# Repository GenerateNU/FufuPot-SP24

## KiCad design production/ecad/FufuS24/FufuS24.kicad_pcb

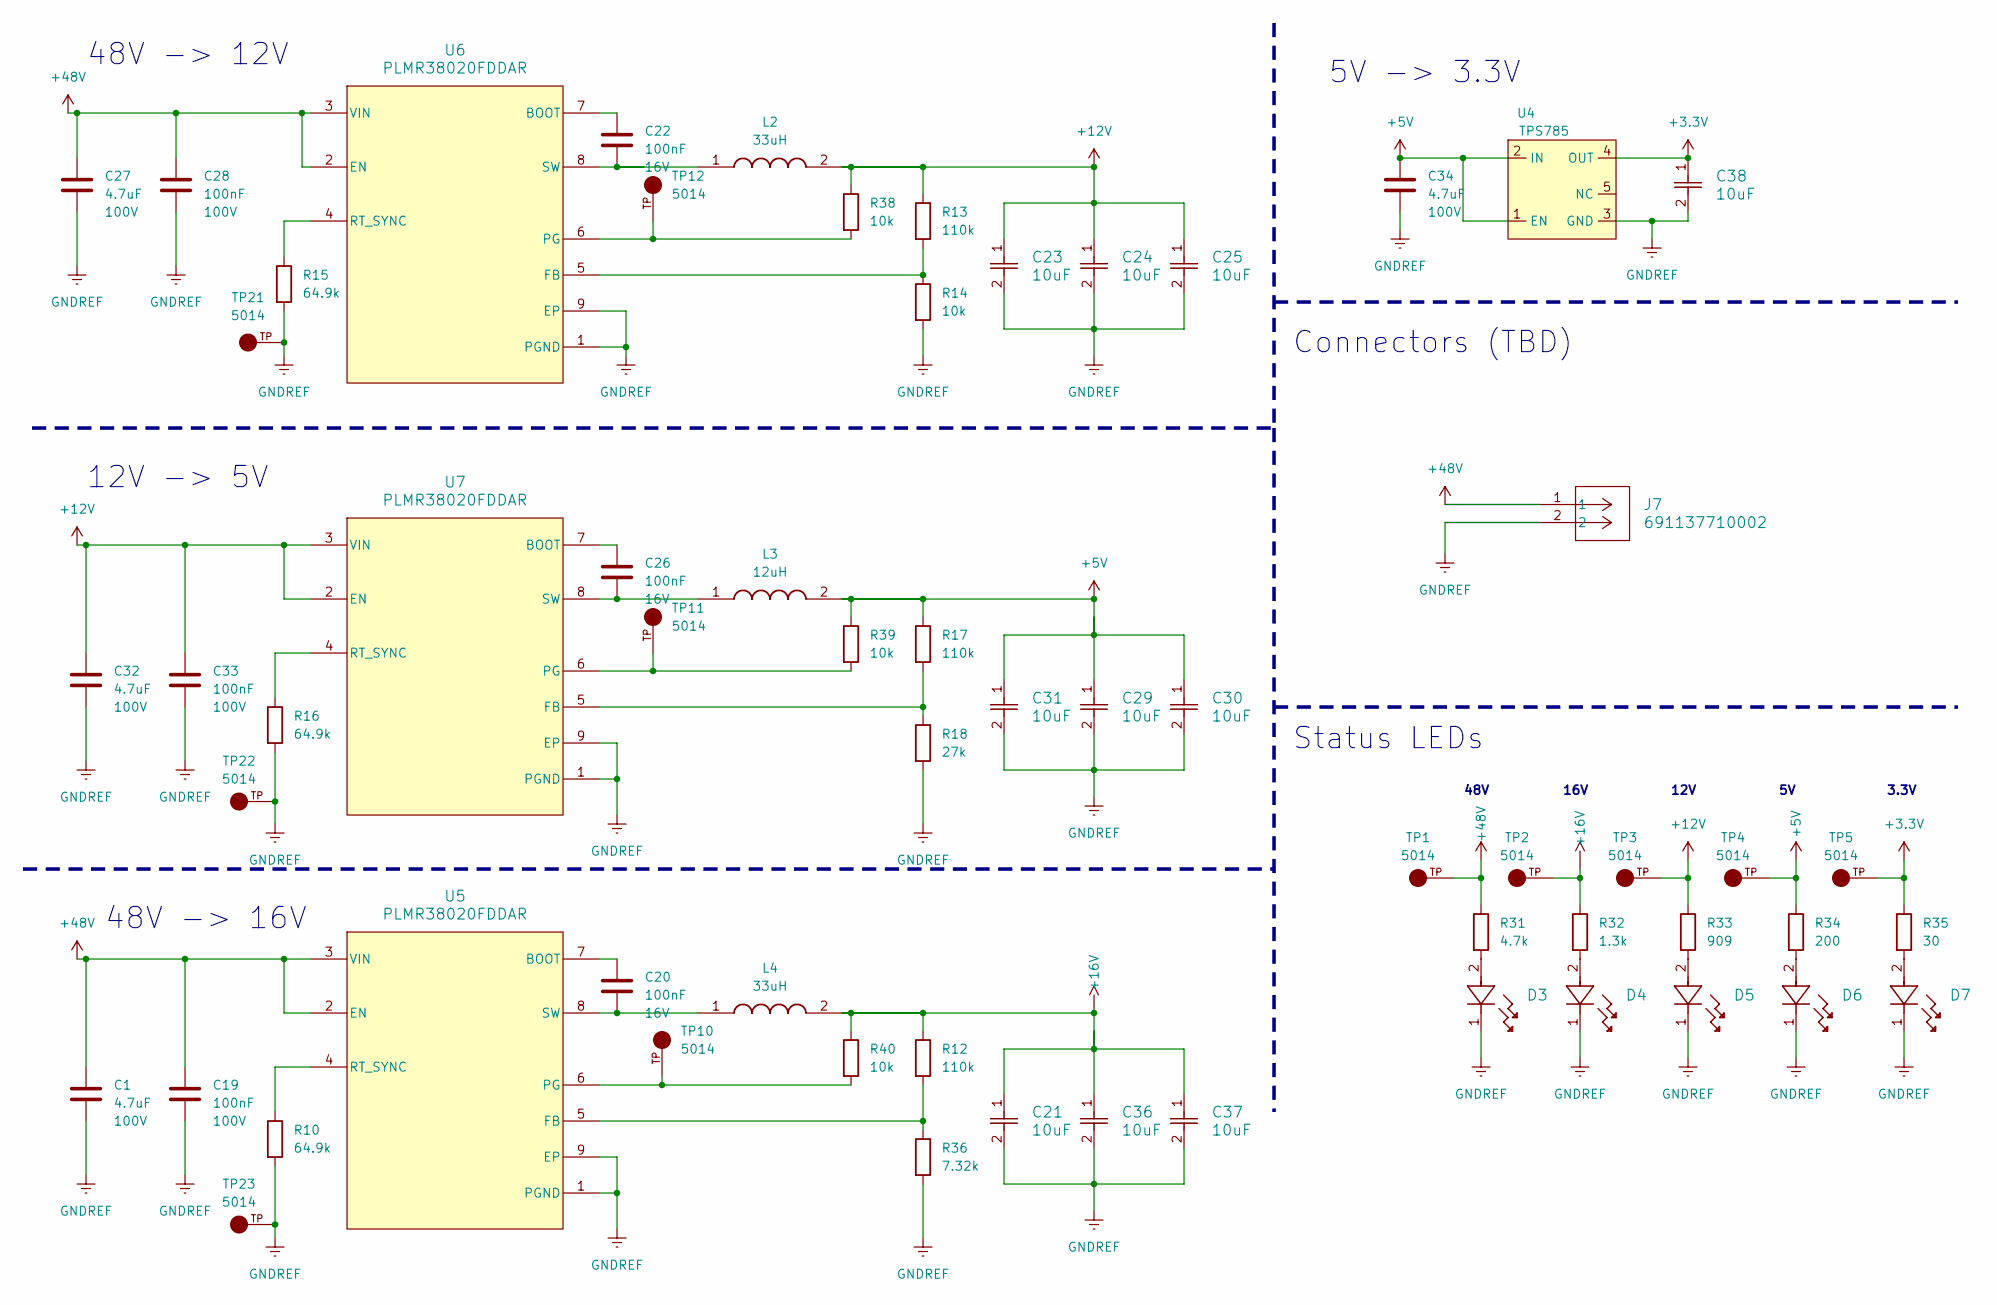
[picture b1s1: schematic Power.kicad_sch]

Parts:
C1, C27, C32, C34: 4.7uF; C_1210_3225Metric; Voltage 100V; MPN KAM32LR72A475KU
C19, C28, C33: 100nF; CAPC2012X94N; Voltage 100V; MPN CL21B104KCFNNNE
C20, C22, C26: 100nF; CAPC2012X94N; Voltage 16V; MPN CL21B104KCFNNNE
C21, C23, C24, C25, C29, C30, C31, C36, C37, C38: 10uF; CAPC2012X94N
D3, D4, D5, D6, D7: 150080GS75000; LED_GS75000_WRE
J7: 691137710002; CONN2_710002_WRE
L2, L4: 33uH; INDPM120120X800N; Manufacturer_Part_Number CDRH127/LDNP-330MC; Mouser Part Number 851-CDRH127LDNP330MC
L3: 12uH; INDPM120120X800N; Manufacturer_Part_Number CDRH127/LDNP-120MC; Mouser Part Number 851-CDRH127LDNP120MC
R10, R15, R16: 64.9k; RESC2012X60N
R12, R13, R17: 110k; RESC2012X60N
R14, R38, R39, R40: 10k; RESC2012X60N
R18: 27k; RESC2012X60N
R31: 4.7k; RESC2012X60N
R32: 1.3k; RESC2012X60N
R33: 909; RESC2012X60N
R34: 200; RESC2012X60N
R35: 30; RESC2012X60N
R36: 7.32k; RESC2012X60N
TP1, TP2, TP3, TP4, TP5, TP10, TP11, TP12, TP21, TP22, TP23: 5014; TP_5014; PARTREV F
U4: TPS785; DPAK114P990X239-6N
U5, U6, U7: PLMR38020FDDAR; DDA0008E-IPC_A

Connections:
+12V: C23.1, C24.1, C25.1, C32.1, C33.1, L2.2, R13.1, R33.1, R38.1, TP3.TP, U7.2 (EN), U7.3 (VIN); also elsewhere on the board
+16V: C21.1, C36.1, C37.1, L4.2, R12.1, R32.1, R40.1, TP2.TP; also elsewhere on the board
+48V: C1.1, C19.1, C27.1, C28.1, J7.1, R31.1, TP1.TP, U5.2 (EN), U5.3 (VIN), U6.2 (EN), U6.3 (VIN); also elsewhere on the board
unnamed: D3.2, R31.2
unnamed: D4.2, R32.2
unnamed: D5.2, R33.2
unnamed: D6.2, R34.2
unnamed: D7.2, R35.2
unnamed: C20.1, U5.7 (BOOT)
unnamed: R12.2, R36.1, U5.5 (FB)
unnamed: R40.2, TP10.TP, U5.6 (PG)
unnamed: R10.1, U5.4 (RT_SYNC)
unnamed: C20.2, L4.1, U5.8 (SW)
unnamed: C22.1, U6.7 (BOOT)
unnamed: R13.2, R14.1, U6.5 (FB)
unnamed: R38.2, TP12.TP, U6.6 (PG)
unnamed: R15.1, U6.4 (RT_SYNC)
unnamed: C22.2, L2.1, U6.8 (SW)
unnamed: C26.1, U7.7 (BOOT)
unnamed: R17.2, R18.1, U7.5 (FB)
unnamed: R39.2, TP11.TP, U7.6 (PG)
unnamed: R16.1, U7.4 (RT_SYNC)
unnamed: C26.2, L3.1, U7.8 (SW)

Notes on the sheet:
16V
48V -> 12V
12V -> 5V
5V -> 3.3V
Status LEDs
48V -> 16V
48V
3.3V
Connectors (TBD)
12V

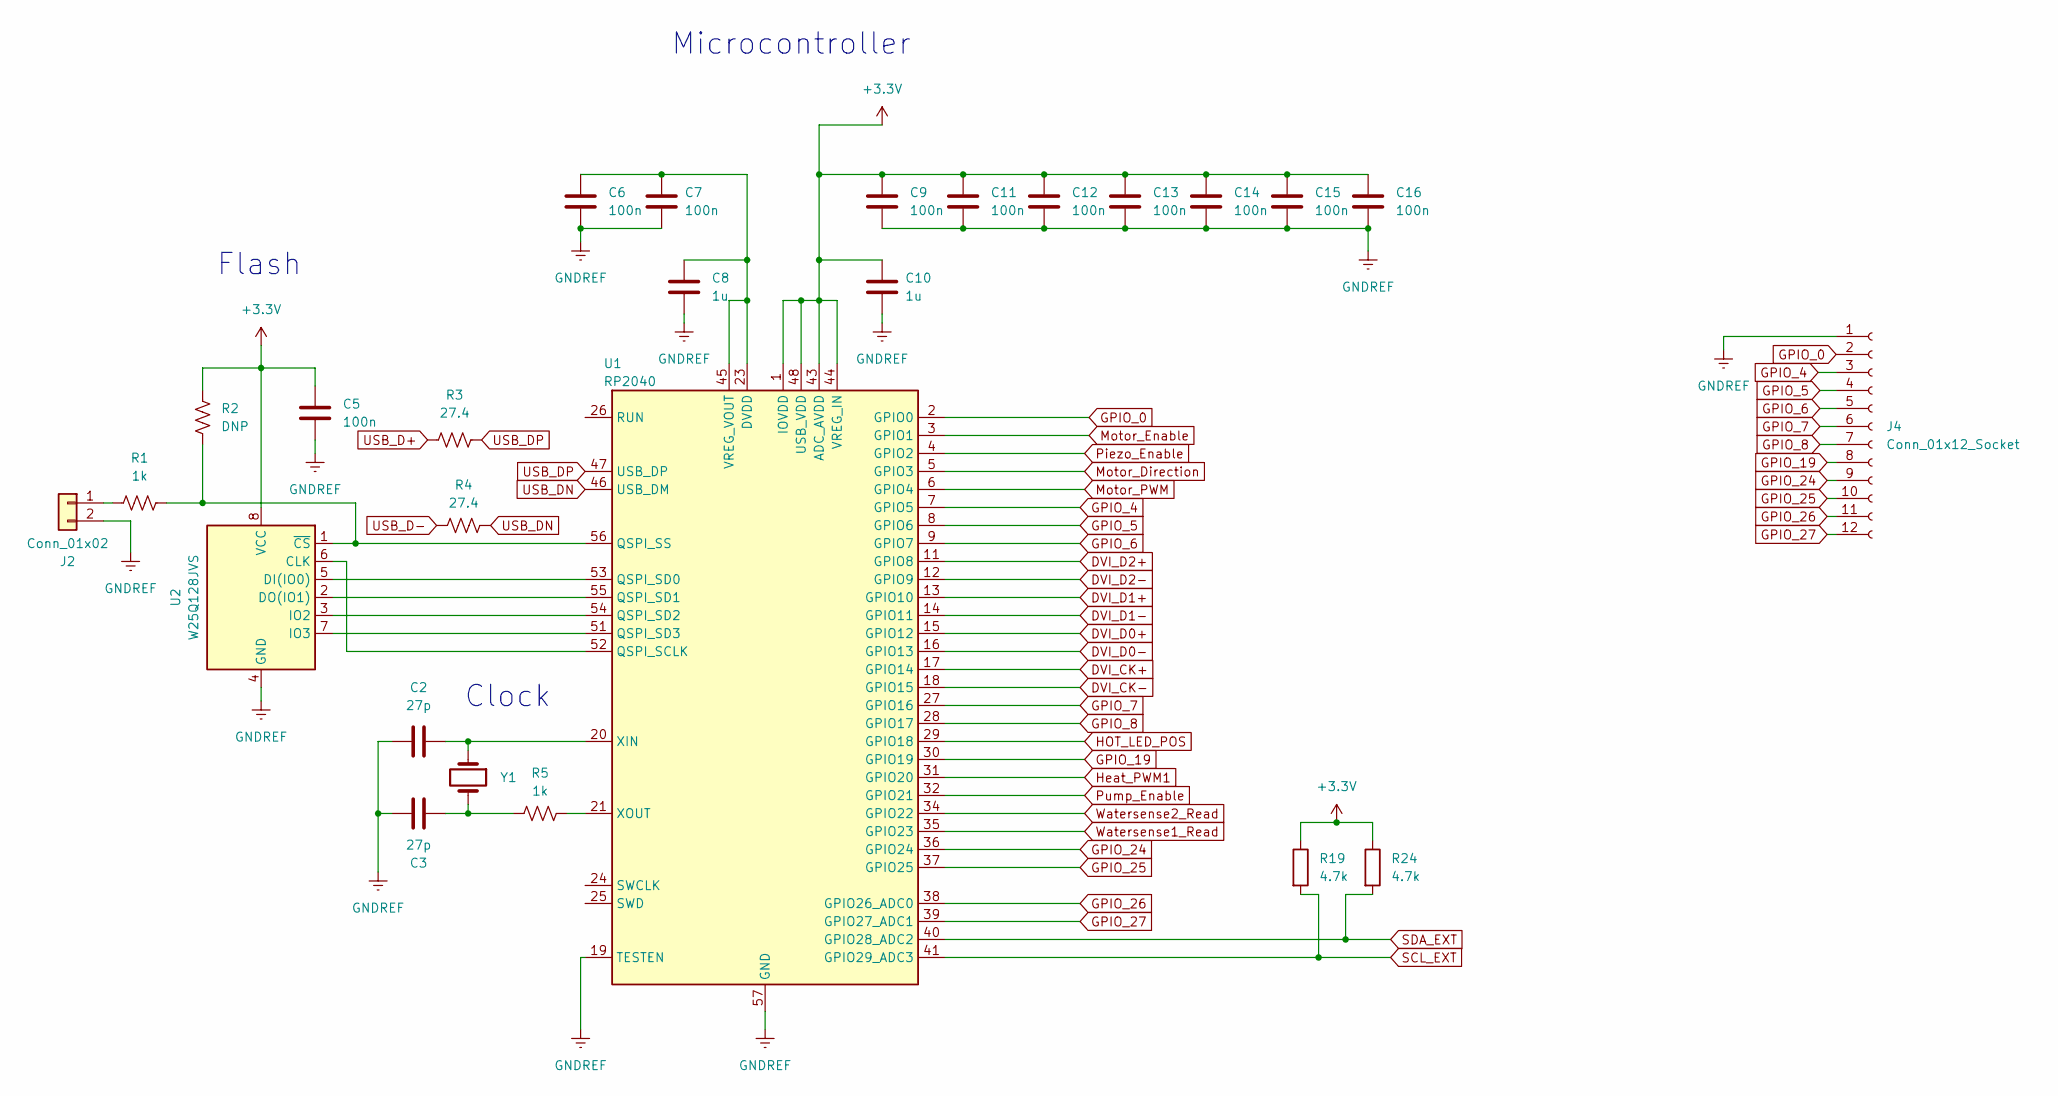
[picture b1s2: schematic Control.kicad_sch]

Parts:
C2, C3: 27p; CAPC2012X94N
C5, C6, C7, C9, C11, C12, C13, C14, C15, C16: 100n; CAPC2012X94N
C8, C10: 1u; CAPC2012X94N
J2: Conn_01x02; CON_5025840270_MOL
J4: Conn_01x12_Socket; PinSocket_1x12_P2.54mm_Vertical
R1, R5: 1k; RESC2012X60N
R2: DNP; RESC2012X60N
R3, R4: 27.4; RESC2012X60N
R19, R24: 4.7k; RESC2012X60N
U1: RP2040; RP2040_Footprint
U2: W25Q128JVS; W25Q128JVSIM_footprint
Y1: XTAL_ABLS-12.000MHZ-B4-T

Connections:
DVI_CK+: U1.17 (GPIO14); also elsewhere on the board
DVI_CK-: U1.18 (GPIO15); also elsewhere on the board
DVI_D0+: U1.15 (GPIO12); also elsewhere on the board
DVI_D0-: U1.16 (GPIO13); also elsewhere on the board
DVI_D1+: U1.13 (GPIO10); also elsewhere on the board
DVI_D1-: U1.14 (GPIO11); also elsewhere on the board
DVI_D2+: U1.11 (GPIO8); also elsewhere on the board
DVI_D2-: U1.12 (GPIO9); also elsewhere on the board
GPIO_0: J4.2, U1.2 (GPIO0)
GPIO_4: J4.3, U1.7 (GPIO5)
GPIO_5: J4.4, U1.8 (GPIO6)
GPIO_6: J4.5, U1.9 (GPIO7)
GPIO_7: J4.6, U1.27 (GPIO16)
GPIO_8: J4.7, U1.28 (GPIO17)
GPIO_19: J4.8, U1.30 (GPIO19)
GPIO_24: J4.9, U1.36 (GPIO24)
GPIO_25: J4.10, U1.37 (GPIO25)
GPIO_26: J4.11, U1.38 (GPIO26_ADC0)
GPIO_27: J4.12, U1.39 (GPIO27_ADC1)
HOT_LED_POS: U1.29 (GPIO18); also elsewhere on the board
Heat_PWM1: U1.31 (GPIO20); also elsewhere on the board
Motor_Direction: U1.5 (GPIO3); also elsewhere on the board
Motor_Enable: U1.3 (GPIO1); also elsewhere on the board
Motor_PWM: U1.6 (GPIO4); also elsewhere on the board
unnamed: C3.2, R5.1, Y1.2
unnamed: J2.1, R1.1
unnamed: U1.52 (QSPI_SCLK), U2.6 (CLK)
unnamed: U1.53 (QSPI_SD0), U2.5 (DI(IO0))
unnamed: U1.55 (QSPI_SD1), U2.2 (DO(IO1))
unnamed: U1.54 (QSPI_SD2), U2.3 (IO2)
unnamed: U1.51 (QSPI_SD3), U2.7 (IO3)
unnamed: R1.2, R2.1, U1.56 (QSPI_SS), U2.1 (~CS)
unnamed: C6.1, C7.1, C8.1, U1.23 (DVDD), U1.45 (VREG_VOUT), U1.50 (DVDD)
unnamed: C2.2, U1.20 (XIN), Y1.1
unnamed: R5.2, U1.21 (XOUT)
Piezo_Enable: U1.4 (GPIO2); also elsewhere on the board
Pump_Enable: U1.32 (GPIO21); also elsewhere on the board
SCL_EXT: R19.2, U1.41 (GPIO29_ADC3); also elsewhere on the board
SDA_EXT: R24.2, U1.40 (GPIO28_ADC2); also elsewhere on the board
USB_D+: R3.1; also elsewhere on the board
USB_D-: R4.1; also elsewhere on the board
USB_DN: R4.2, U1.46 (USB_DM)
USB_DP: R3.2, U1.47 (USB_DP)
Watersense1_Read: U1.35 (GPIO23); also elsewhere on the board
Watersense2_Read: U1.34 (GPIO22); also elsewhere on the board

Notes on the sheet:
Microcontroller
Flash
Clock

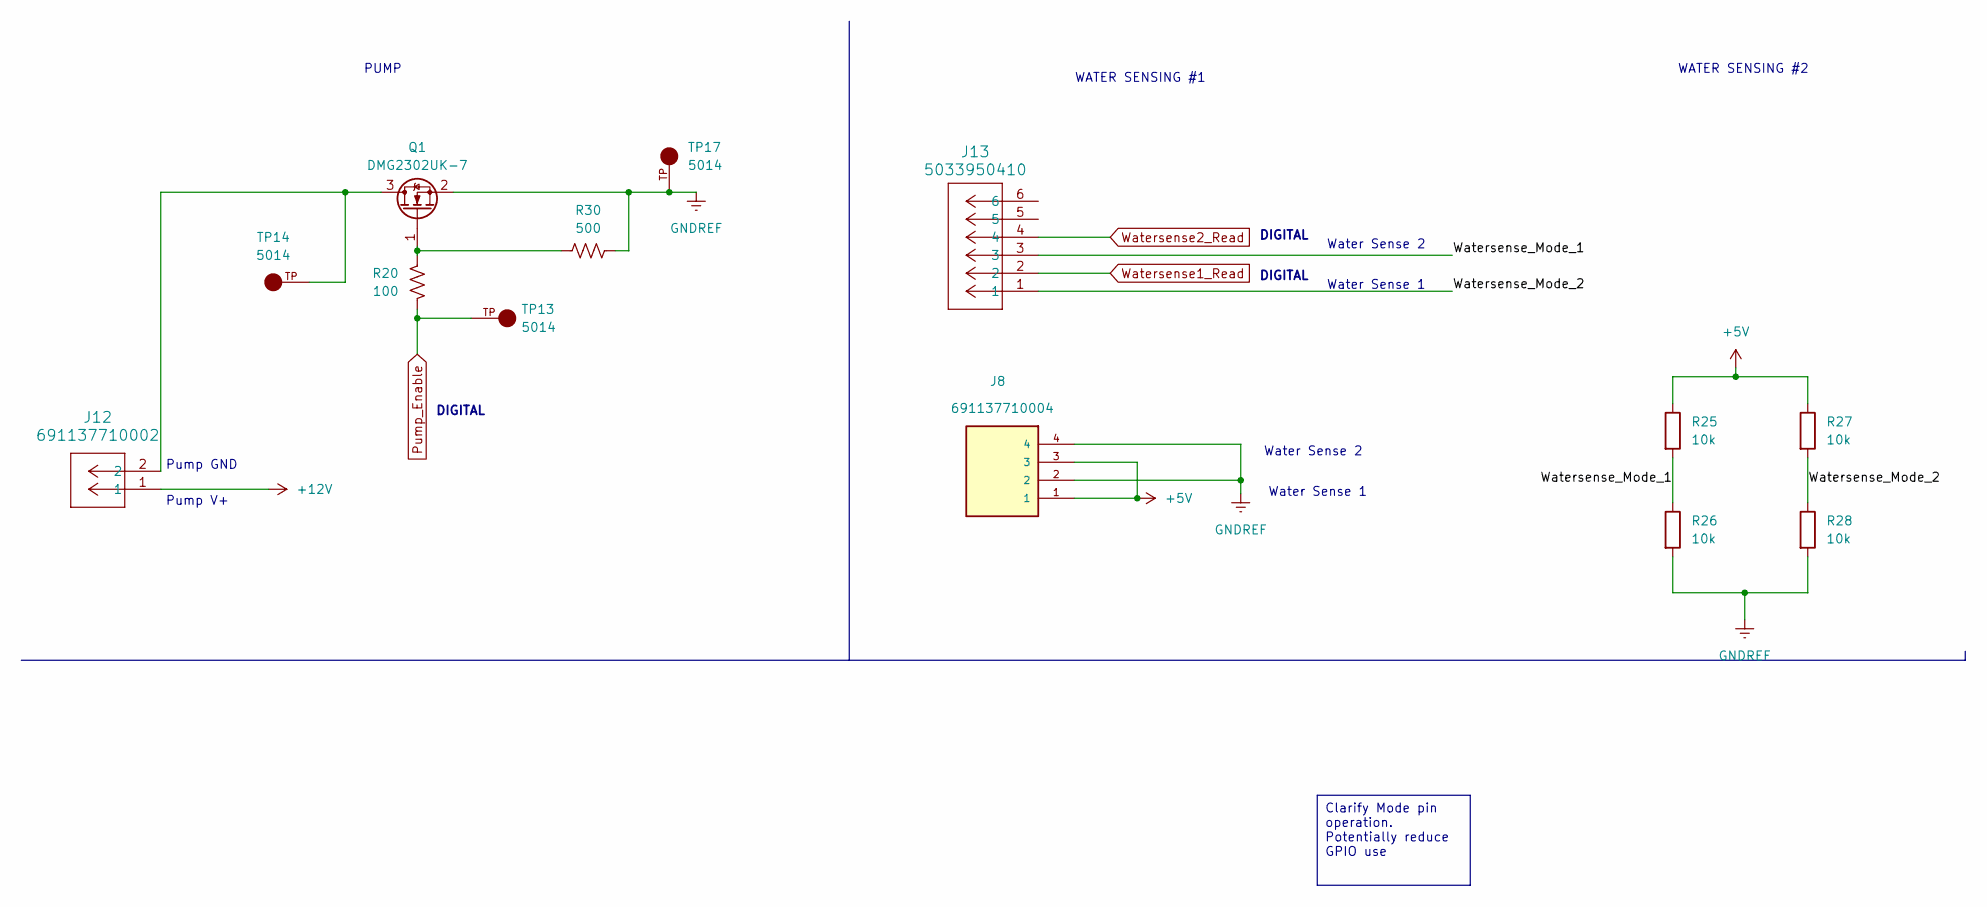
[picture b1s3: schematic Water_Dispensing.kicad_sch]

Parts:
J8: 691137710004; PWR_4POS; PARTREV 001
J12: 691137710002; CONN2_710002_WRE
J13: 5033950410; MOLEX4_CON_5033950410
Q1: DMG2302UK-7; DMG2302UK-7_Footprint
R20: 100; RESC2012X60N
R25, R26, R27, R28: 10k; RESC2012X60N
R30: 500; RESC2012X60N
TP13, TP14, TP17: 5014; TP_5014; PARTREV F

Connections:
+12V: J12.1; also elsewhere on the board
unnamed: J12.2, Q1.3 (D), TP14.TP
unnamed: Q1.1 (G), R20.1, R30.1
Pump_Enable: R20.2, TP13.TP; also elsewhere on the board
Watersense1_Read: J13.2; also elsewhere on the board
Watersense2_Read: J13.4; also elsewhere on the board

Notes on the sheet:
Clarify Mode pin operation. Potentially reduce GPIO use
Water Sense 1
Pump V+
PUMP
Water Sense 2
WATER SENSING #1
DIGITAL
Pump GND
WATER SENSING #2

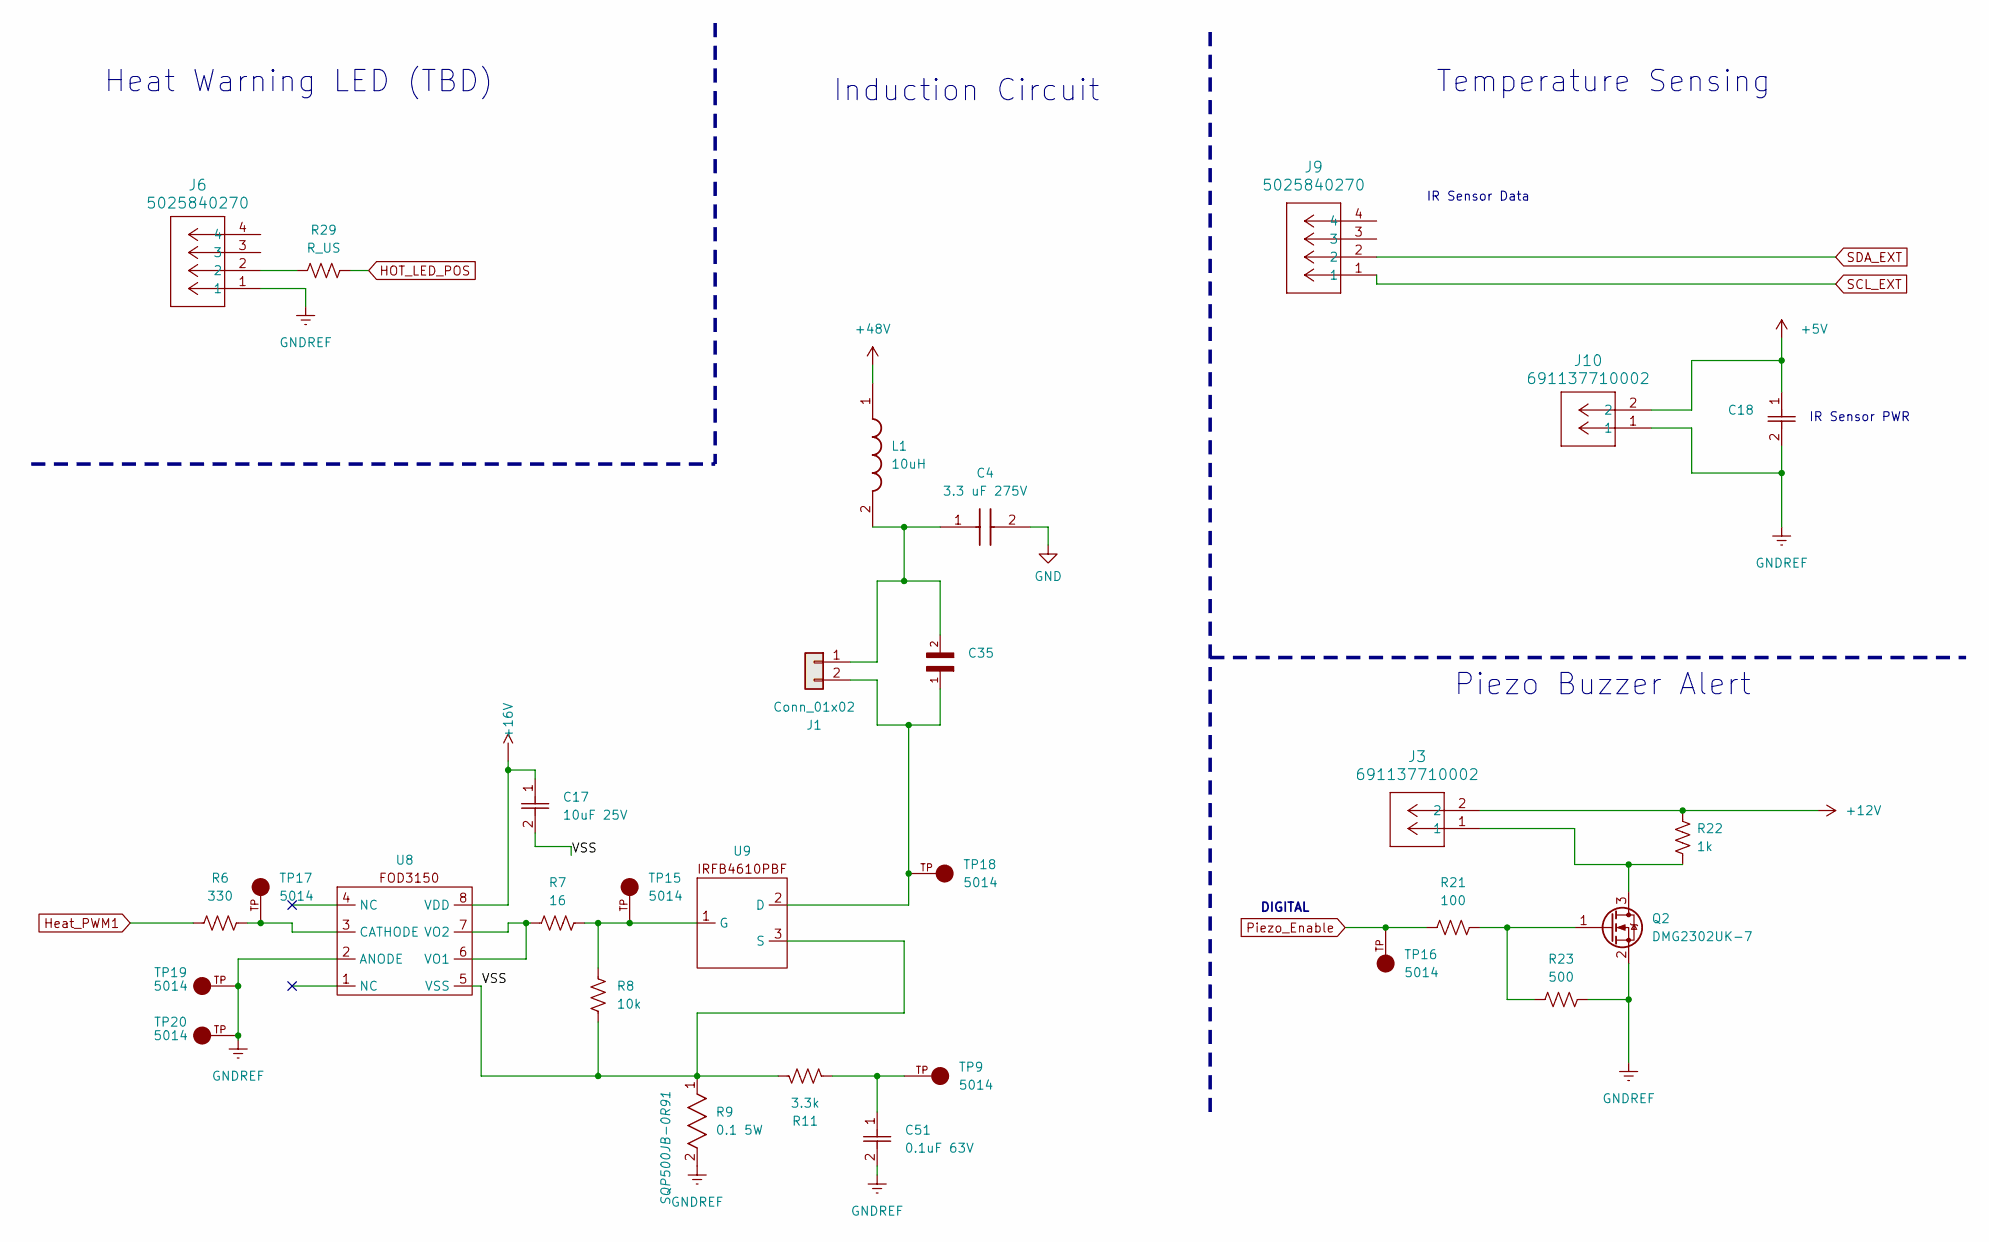
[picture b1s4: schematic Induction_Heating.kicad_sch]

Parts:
C4: 3.3 uF 275V; CAP_ECQUA_41.0LX15.0TX30.0H_PAN; Manufacturer_Part_Number ECQUAAF335LD
C17: 10uF 25V; CAPC2012X94N
C18, C51: 0.1uF 63V; CAPC2012X94N
C35: ECWF6754HL; CAPRR2500W80L2800T1330H1990; PARTREV 11-Oct-17
J1: Conn_01x02; CONN2_710002_WRE
J3, J10: 691137710002; CONN2_710002_WRE
J6, J9: 5025840270; CON_5025840270_MOL
L1: 10uH; INDPM120120X800N; Manufacturer_Part_Number SRP1770CC-100M
Q2: DMG2302UK-7; DMG2302UK-7_Footprint
R6: 330; RESC2012X60N
R7: 16; RESC2012X60N
R8: 10k; RESC2012X60N
R9: 0.1 5W; RES_SQP500_22X9P5_YAG
R11: 3.3k; RESC2012X60N
R21: 100; RESC2012X60N
R22: 1k; RESC2012X60N
R23: 500; RESC2012X60N
R29: R_US; RESC2012X60N
TP9, TP15, TP16, TP17, TP18, TP19, TP20: 5014; TP_5014; PARTREV F
U8: FOD3150_footprint
U9: IRFB4610PBF

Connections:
+12V: J3.2, R22.1; also elsewhere on the board
+16V: C17.1, U8.8 (VDD); also elsewhere on the board
+48V: L1.1; also elsewhere on the board
/Induction Heating/VSS: C17.2, R8.1, R9.1, R11.1, U8.5 (VSS), U9.3 (S)
GND: C4.2
HOT_LED_POS: R29.2; also elsewhere on the board
Heat_PWM1: R6.1; also elsewhere on the board
unnamed: C51.1, R11.2, TP9.TP
unnamed: C4.1, C35.2, J1.1, L1.2
unnamed: C35.1, J1.2, TP18.TP, U9.2 (D)
unnamed: J6.2, R29.1
unnamed: J3.1, Q2.3 (D), R22.2
unnamed: Q2.1 (G), R21.2, R23.1
unnamed: R7.1, U8.6 (VO1), U8.7 (VO2)
unnamed: R7.2, R8.2, TP15.TP, U9.1 (G)
Piezo_Enable: R21.1, TP16.TP; also elsewhere on the board
SCL_EXT: J9.1; also elsewhere on the board
SDA_EXT: J9.2; also elsewhere on the board

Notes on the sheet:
DIGITAL
Heat Warning LED (TBD)
IR Sensor Data
IR Sensor PWR
Induction Circuit
Temperature Sensing
Piezo Buzzer Alert

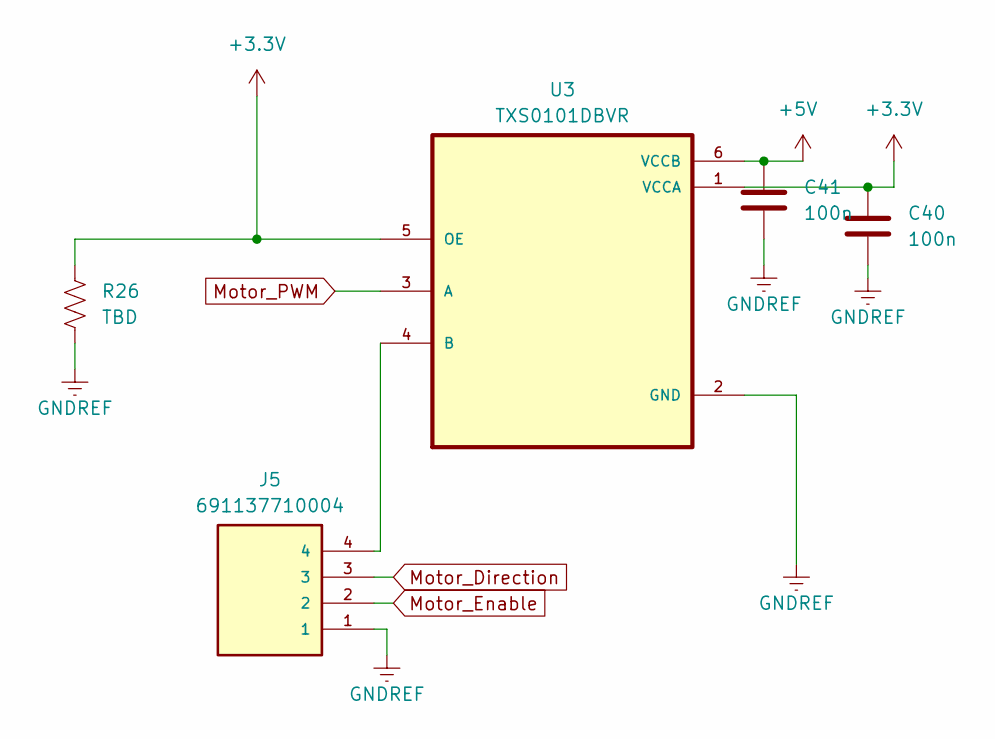
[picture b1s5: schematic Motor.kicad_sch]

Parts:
C40, C41: 100n; WCAP-CSGP_885012206026
J5: 691137710004; PWR_4POS; PARTREV 001
R26: TBD; RESC2012X60N
U3: TXS0101DBVR; LevelShifter_Motor

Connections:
Motor_Direction: J5.3; also elsewhere on the board
Motor_Enable: J5.2; also elsewhere on the board
Motor_PWM: U3.3 (A); also elsewhere on the board
unnamed: J5.4, U3.4 (B)

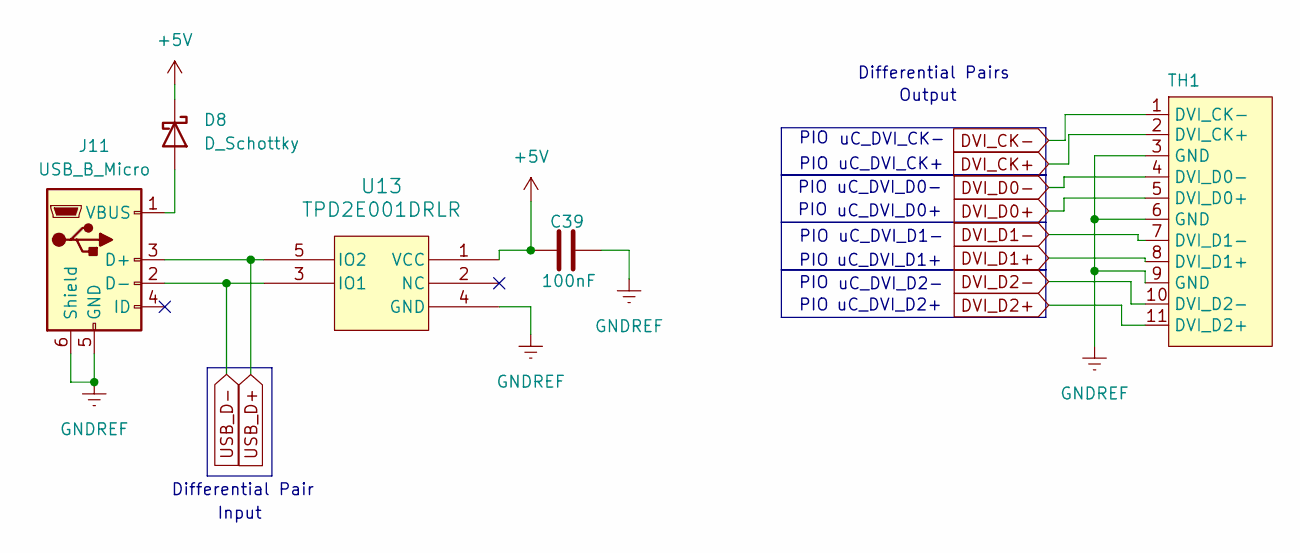
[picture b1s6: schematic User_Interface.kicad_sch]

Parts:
C39: 100nF; C_0805_2012Metric
D8: D_Schottky; D_SMA
J11: USB_B_Micro; USB_Micro-B_Molex-105017-0001
TH1: PinSocket_1x11_P2.54mm_Vertical
U13: TPD2E001DRLR; Texas_R-PDSO-N5_DRL-5

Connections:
DVI_CK+: TH1.2 (DVI_CK+); also elsewhere on the board
DVI_CK-: TH1.1 (DVI_CK-); also elsewhere on the board
DVI_D0+: TH1.5 (DVI_D0+); also elsewhere on the board
DVI_D0-: TH1.4 (DVI_D0-); also elsewhere on the board
DVI_D1+: TH1.8 (DVI_D1+); also elsewhere on the board
DVI_D1-: TH1.7 (DVI_D1-); also elsewhere on the board
DVI_D2+: TH1.11 (DVI_D2+); also elsewhere on the board
DVI_D2-: TH1.10 (DVI_D2-); also elsewhere on the board
USB_D+: J11.3 (D+), U13.5 (IO2); also elsewhere on the board
USB_D-: J11.2 (D-), U13.3 (IO1); also elsewhere on the board

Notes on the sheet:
Differential Pairs
PIO
uC_DVI_CK+
Input
uC_DVI_D0+
Output
uC_DVI_D1-
uC_DVI_D1+
uC_DVI_D0-
uC_DVI_D2-
uC_DVI_D2+
Differential Pair
uC_DVI_CK-

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
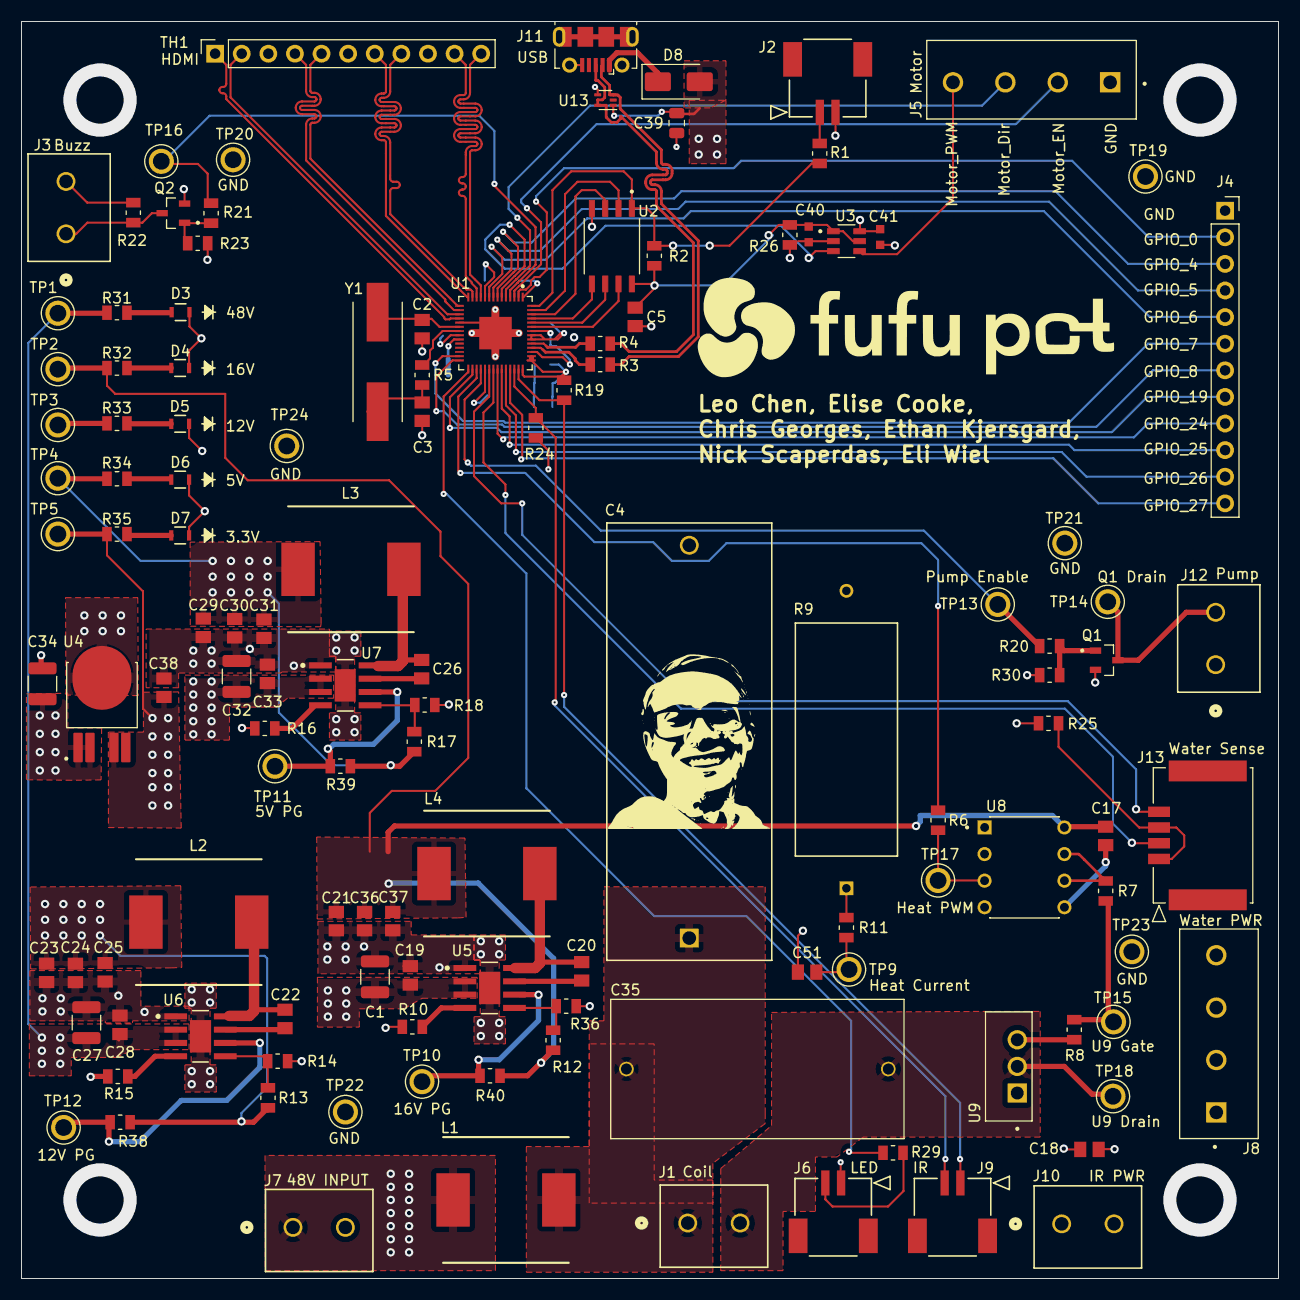
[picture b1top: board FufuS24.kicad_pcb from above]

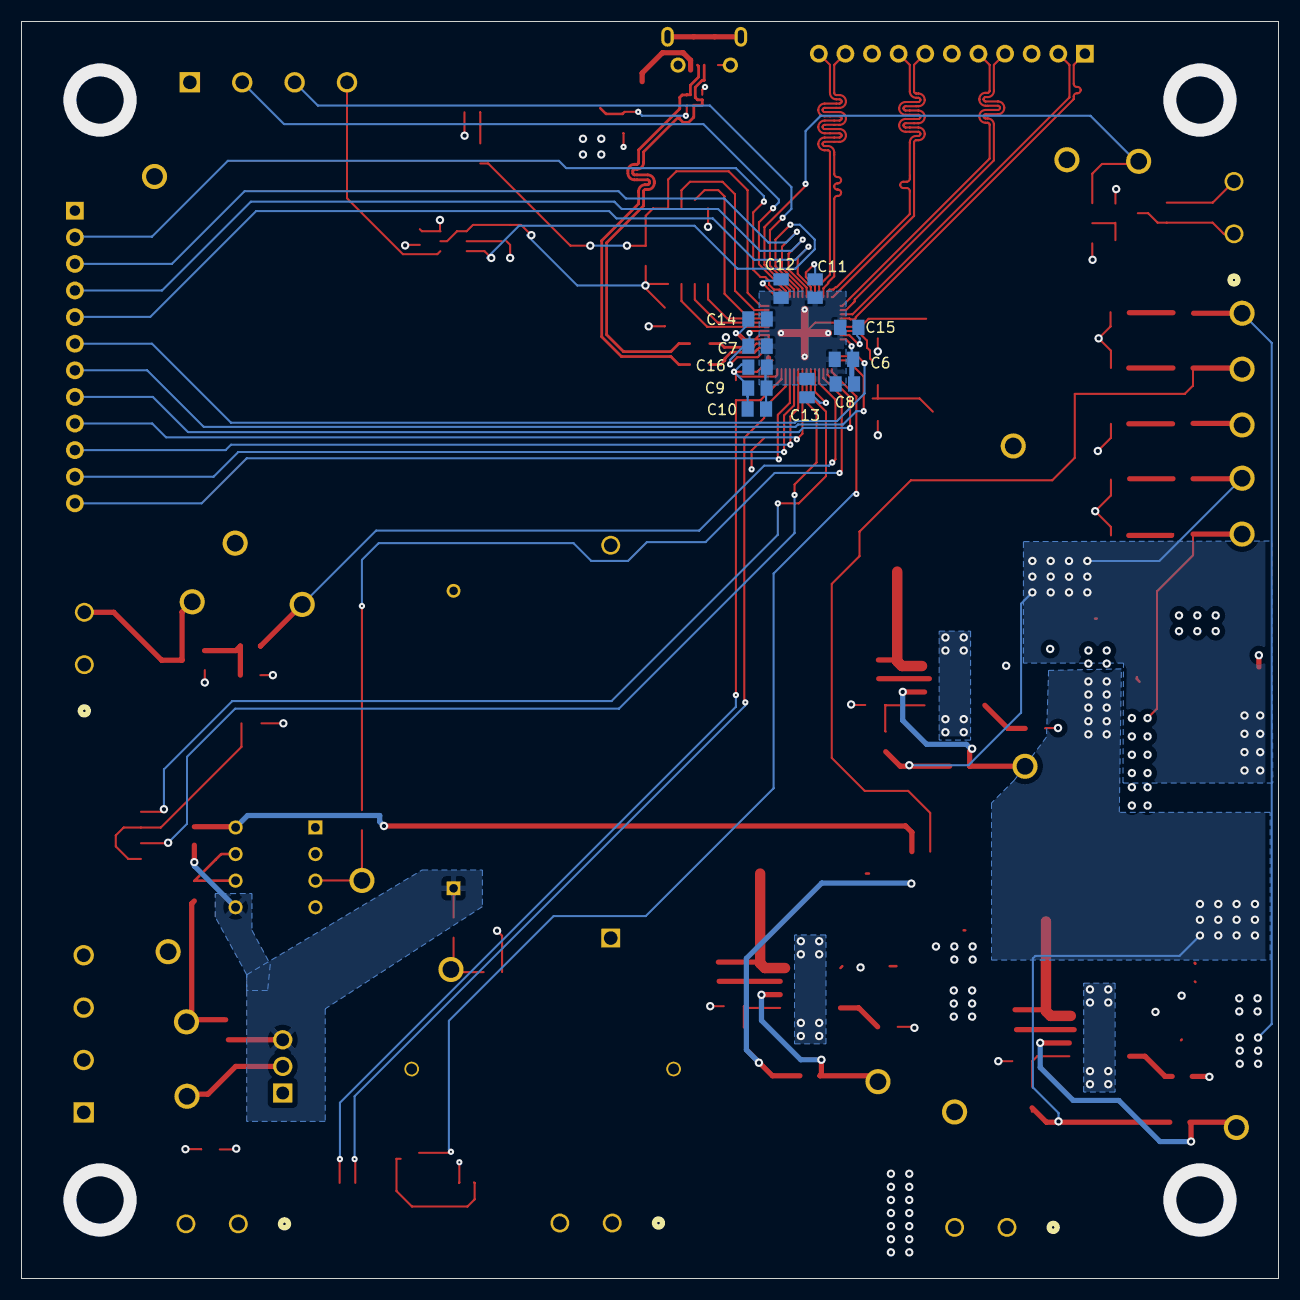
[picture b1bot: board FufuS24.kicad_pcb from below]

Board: 4 copper layers, 120.0 x 120.0 mm, 137 parts (11 on the bottom side), 86 nets.

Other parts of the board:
TP24: 5014; TP_5014

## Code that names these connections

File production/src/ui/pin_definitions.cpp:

#include "pin_definitions.h"


void initialize_gpios() {
    gpio_init(gpio_0);
    gpio_init(motor_en);
    gpio_init(piezo_en);
    gpio_init(motor_dir);
    gpio_init(motor_pwm);
    gpio_init(gpio_4);
    gpio_init(gpio_5);
    gpio_init(gpio_6);
    gpio_init(dvi_d2_pos);
    gpio_init(dvi_d2_neg);
    gpio_init(dvi_d1_pos);
    gpio_init(dvi_d1_neg);
    gpio_init(dvi_d0_pos);
    gpio_init(dvi_d0_neg);
    gpio_init(dvi_ck_pos);
    gpio_init(dvi_ck_neg);
    gpio_init(gpio_7);
    gpio_init(gpio_8);
    gpio_init(hot_led_pos);
    gpio_init(gpio_19);
    gpio_init(heat_pwm);
    gpio_init(pump_en);
    gpio_init(watersense_2_read);
    gpio_init(watersense_1_read);
    gpio_init(gpio_24);
    gpio_init(gpio_25);
    gpio_init(gpio_26);
    gpio_init(gpio_27);
    gpio_init(sda_ext);
    gpio_init(scl_ext);
}

void set_gpio_funcs() {
    //water pins
    gpio_set_dir(pump_en, 1);
    //write pump to low just in case
    gpio_put(pump_en, 0);
    gpio_set_dir(watersense_2_read, 0);
    gpio_set_dir(watersense_1_read, 0);

    //Piezo Buzzer
    gpio_set_dir(piezo_en, 1);
    gpio_put(piezo_en, 0);

    //LED
    gpio_set_dir(hot_led_pos, 1);
    gpio_put(hot_led_pos, 0);

    //motor 
    gpio_set_dir(motor_en, 1);
    //write motor to low just in case
    gpio_put(motor_en, 0);
    gpio_set_dir(motor_dir, 1);
    //Sets motor to counterclockwise
    gpio_put(motor_dir, 0);
    gpio_set_function(motor_pwm, GPIO_FUNC_PWM);


    //heating pins
    gpio_set_function(heat_pwm, GPIO_FUNC_PWM);

    //TO-DO -> SET FUNCTIONS FOR DVI PINS

    //i2c pins
    gpio_set_function(sda_ext, GPIO_FUNC_I2C);
    gpio_set_function(scl_ext, GPIO_FUNC_I2C);
}

uint32_t pwm_set_freq_duty(int slice_num, int chan, uint32_t f, int d) {
    uint32_t clock = 12000000;
    uint32_t divider16 = clock / f / 4096 + (clock % (f * 4096) != 0);
    if (divider16 / 16 == 0) {
        divider16 = 16;
    }
    uint32_t wrap = clock * 16 / divider16 / f - 1;
    pwm_set_clkdiv_int_frac(slice_num, divider16/16, divider16 & 0xF);
    pwm_set_wrap(slice_num, wrap);
    pwm_set_chan_level(slice_num, chan, wrap * d / 100);
    return wrap;
}

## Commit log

2024-02-03 KiCad Hierarchical Schematic
    Pushing the barebones initial KiCad file to git, it contains a root schematic which houses the 6 electrical subsystems as other schematic pages, which are all blank
2024-02-04 Update Control.kicad_sch
    Microcontroller Schematic progress
2024-02-16 added heating schematic notes
2024-02-16 updated footprint library
2024-02-16 Added new modules and finished first draft of 16V converter
2024-02-16 worked on power page
2024-02-17 Finished first draft of power page
2024-02-19 rp2040 symbol and footprint
2024-02-19 updated symbol and footprint libraries to use relative paths and hopefully fix issues...
2024-02-20 added rp2040 to schematic
2024-02-20 Water Sensing Added
    Lots of global labels to symbolize wires going from 5V and GPIO to water sensor
2024-02-20 Motor Schematic V1
    if you're reading this AAAAAAAAAAAAAAAAAAAAAAAAAAAAAAAAAAAAAAAAAAAAAAAAAAAAAAAAAAAAAAAAAAAAAA
2024-02-21 Efan
2024-02-21 Water Dispensing Draft1
    Added Pump Control, Symbols for Schottkey diode (may need to change to smaller package), added text to show where gpio pins go
2024-02-21 added micro usb, LDO regulator, and HDMI
2024-02-21 Updated Motor
2024-02-21 Updated heating cap
2024-02-21 Added flags and connections to HDMI
2024-02-22 removed diode, replaced with gate resistor
    i like dinosaurs
    transistor already had gate protection
2024-02-22 Update User_Interface.kicad_sch
    Fixed power to mUSB and HDMI
2024-02-22 Updated Ctrl and UI schems
    Added labels to Control and changed nets to output. Updated GPIO pins on UI to reflect what was available.
2024-02-22 Update User_Interface.kicad_sch
    Removed decoupling cap for 5V on UI it might be redundant
2024-02-23 Design review changes
2024-02-23 changed port names
2024-02-23 changed port names again
2024-02-23 added resistors to HDMI
2024-02-23 changed global label names water
    what the summary said
2024-02-23 gpio pin names for motor
2024-02-23 okay like actual water changes
2024-02-23 updated control and UI flags
2024-02-24 fixed my schematic
    UI now working after fixing symbols and stuff
2024-02-24 added PIO and removed CEC
2024-02-24 Ethan Stuff
2024-02-24 added LEDs
2024-02-26 Incorporated schematic review feedback
2024-02-26 updated some MPNs
2024-02-26 cleaned up schematic
2024-02-27 Added labels for diff pairs
2024-02-27 Adding pullup resistors to I2C bus 1
2024-02-27 Changing spacing on control
2024-02-27 Added feedback notes
2024-02-27 Added coupling caps to HDMI
2024-02-27 Ethan Changes
2024-03-01 Added ESD diodes to UI schem
2024-03-02 added ESD and diodes but idk if correctly done
2024-03-02 removed notes from UI schem
2024-03-03 efan 2
2024-03-03 efan 3
2024-03-03 efaa 4
2024-03-03 goose
2024-03-03 efan 5
2024-03-03 Efan 6
2024-03-03 elise connector
2024-03-03 efan 7
2024-03-03 eLISE MOTOR FIXED
2024-03-03 efan 8
2024-03-03 Revert "efan 8"
    This reverts commit dcd24bf40ef329a5e9c1d5f3e5ec1a05c3beec39.
2024-03-03 SUre
2024-03-03 efan 9
2024-03-03 Footprints
2024-03-03 Final Foot Fetish
2024-03-05 efan finals before laying out
2024-03-05 efab "we layed out"
2024-03-05 efan part 2 laying out
2024-03-11 efan laying out
2024-03-11 laying out
2024-03-12 lAYOUT
2024-03-13 Layout progress (no mcu or hdmi)
2024-03-13 Staring MCU routing
2024-03-15 updated symbols for throughholes
    updated ui
2024-03-15 updated symbols for through hole
2024-03-15 updated symbols and footprints for UI
2024-03-15 aaa???
2024-03-15 TRUST FALL
2024-03-15 if you're reading this aaaaaaa
2024-03-15 Layout update 3/15 morning
2024-03-15 piezo changes
2024-03-15 Made GPIO changes
2024-03-16 Revert "initial commit"
    This reverts commit ad785483ccb177511be69b6ed188aed901e4a07f.
2024-03-16 fixing traces
2024-03-16 Component placement for piezo
2024-03-17 experimenting with submoduels
2024-03-17 removing picodvi submodule
2024-03-17 adding custom picodvi files
2024-03-17 testing push
2024-03-17 editing cmake list for fufu-ui test file
2024-03-17 Big layout push
2024-03-17 few more layout changes:
2024-03-18 major layout changes
2024-03-18 More layout work
2024-03-18 HDMI + USB
2024-03-18 updated planes
2024-03-19 review changes
2024-03-19 created heat control file and cleaned up main a smidgen
2024-03-19 revised high speed signals
2024-03-19 add 3d model for micro usb port
2024-03-19 swapped layers
2024-03-20 updated water sensor
2024-03-20 i am pulling my hair out
2024-03-20 updated layout
2024-03-20 updated power planes
2024-03-21 fixed some DRC
2024-03-21 adding more thinking and skeleton code too tired
2024-03-21 fixed all design rules violations
2024-03-21 Fixed HDMI
2024-03-21 silkscreen
2024-03-21 added heat control convert temp func, understanding more
2024-03-22 silkscreen changes
2024-03-22 'important' silkscreen changes
2024-03-22 pushing headers and more heat ctrl code
2024-03-22 push (moans)
    xs
2024-03-22 updated inductor
2024-03-22 button
2024-03-22 layout eli plz
2024-03-22 more
2024-03-23 revert change to .gitmodules
2024-03-24 more comments to heat control
2024-03-24 troubleshooting submodules
2024-03-28 continuing developing heat control code
2024-03-29 more heating code and reformating to make more sense
2024-03-29 more refactoring, trying to make things most optimized
2024-04-01 code location labeled
2024-04-01 cleaned up syntax
2024-04-01 added comment
2024-04-01 type fixes
2024-04-01 fixing gpio code
2024-04-01 editing cmake to include lvgl
2024-04-02 embedded test
2024-04-02 fuck that file
2024-04-05 fuck leos code i had to comment it all out to build
2024-04-06 updated heating code with tested and functional code
2024-04-12 name change
2024-04-12 added header files
2024-04-12 added pin definitons
2024-04-12 added cpp files
2024-04-13 changes april 11
2024-04-13 updating includes
2024-04-13 updating includes again
2024-04-13 added all 3D models
2024-04-14 changed pin defintions file
2024-04-14 editing includes
2024-04-14 new funcs
2024-04-14 water code + pin path change for my sanity
2024-04-14 moving function body from .h to .cpp
2024-04-15 changed comment style
2024-04-15 more comments
2024-04-16 idk prob a lot of changes
2024-04-16 ifndef additions
2024-04-16 cooking function added, small edits elsewhere
2024-04-16 commented out i2c code so id stop getting errors
2024-04-16 set digital pins to low just in case
2024-04-16 deleted soft, regular, firm cook functions
2024-04-16 more comments for each pin constant
2024-04-16 setting more functions of pins
2024-04-17 change motor pin definition
2024-04-17 changed freq variables
2024-05-04 Final code
2024-05-07 moving files out of ui folder
